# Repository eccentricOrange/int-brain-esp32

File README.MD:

# Integrated Brain ESP-IDF Component
This is the MCU firmware for a custom PCB designed to control, supply power to, and monitor a four-wheeled robot. It's built on a master-slave architecture, with an ESP32 as the slave and an SBC (such as an NVIDIA Jetson or Raspberry Pi) as the master.

Related projects:
-   [Integrated Brain PCB](https://github.com/eccentricOrange/int-brain)
-   [Integrated Brain Python Library](https://github.com/eccentricOrange/int-brain-sbc)

Note that this project has a lot of different registers, addresses, and buffers. These are referenced several times throughout the documentation, but in the interest of comprehensibility, they are all listed towards the end of the documentation only.

# Overall design
Let's get an overview of the different concepts and categories of stuff (such as functions) involved in this component.

## Direct and register-based tasks
In general, there are two types of functions in the component:

-   **Direct task**

    These functions are typical functions. You call them (and pass in arguments if relevant) and the function will try to do whatever you told it to. Exactly how it behaves is completely transparent in this scenario: for example, if you told motor 3 to move forward with a PWM of 127, that's exactly what the system will attempt to do, and nothing else.

-   **Register-based task**

    In the interest of having a flexible system that can establish duplex (two-way) communication with an SBC, there is an extensive system of registers and state variables. Many functions write to these, and many others read from them to decide what actions to perform. You (the programmer) doesn't have the luxury of specifying the 127 (PWM) or forward (direction) as literal values in this situation.

The Doxygen documentation for each function states its type, so you can easily tell which is which.

## Topics/themes

*   **PCA9635 PWM Demux**

    To overcome the low number of GPIOs in the ESP32, this project uses the PCA driver to give PWM signals to the motor drivers and their corresponding LEDs. There are methods around initializing the driver, setting it's mode, setting specific PWM values etc. These are all under `pca_driver.h`.

*   **Current sense**

    The motor drivers have a current sense output that can be read by the ESP32 (with the use of a shunt resistor). The current sense is read by the ADC and converted to a digital value. The initialization, calibration, and reading of the current sense are all under `current_sense.h`.

*   **Encoder**
    
    The motors have encoders that can be read by the ESP32 to provide their angular velocity. The initialization, reading, and resetting of the encoders are all under `encoder.h`.

*   **Control of the robot and that of the motors is separate**

    The PCA drivers file `pca_driver.h` is responsible for controlling the motors and LEDs, and tends to deal with the lower-level functions of one motor at a time. The `four-wheel-robot.h` file is responsible for controlling four motors at a time, and includes some functions to instead treat the system as a cohesive robot. Functions in `four-wheel-robot.h` use functions from `pca_driver.h` quite heavily.

*   **Structure**

    In general, "direct" functions are used to handle things like initialization and register-based functions are used to handle the actual tasks. Either these functions directly, or your custom functions, are expected to be registered as RTOS tasks using `xTaskCreate()` (built-in to FreeRTOS and ESP-IDF) since they will run perpetually.

# I2C Communication with the SBC
This is one of the relatively elaborate parts of the firmware, so it deserves some more attention. In general, the ESP32 acts as a slave to the SBC. The SBC can both issue commands to the ESP32, and request data such as sensor readings and motor status.

It is important you understand how this works, so we'll go over it in detail.

*   **The concept of a pseudo register**

    In the world of I2C-based devices, it is common for the slave to have a register. Each register then has a defined memory location (an address) and a clear purpose. For example, setting the value of the register at `0x00` sets the PCA driver mode, telling it what to do with further commands from the master.

    Since there is a wide variety of data we wish to transfer between the ESP32 and the SBC, this project adopts a similar system. Instead of dealing with actual memory addresses in the ESP32, we use a "pseudo register" system. To the SBC, this seems as though the ESP32 has registers like any ol' I2C device. However, in reality, it just places the byte that's supposed to the register address into a `switch() case` structure.

    Many other functions in the firmware behave in that way, so it's important to recognize what the term "register" refers to in this system. Unfortunately, devices like the PCA driver and the IMU do have true registers, so I'll provide a list of all pseudo later in this documentation.

    `int-brain-sbc-registers.h` gives the addresses of most of these pseudo registers that the SBC has to deal with. Additionally, addresses are split into sending and receiving addresses, to make it easier to determine what the I2C bus is doing at any given time.

*   **I2C buffers**

    Additionally, whenever the master (SBC) initiates a communication, it is expected that the first byte is the pseudo register address. The ESP32 will then read this byte and decide what to do based on it. While parsing, this byte is stored in `_sbc_i2c1_register`.

    Keeping in mind the interrupt-based nature of I2C communication in the ESP32 system \[[source](https://docs.espressif.com/projects/esp-idf/en/v5.3/esp32/api-reference/peripherals/i2c.html)\], two I2C buffers are defined in this system.

    *   One of them `_sbc_i2c1_receive_buffer` is the data (such as motor speeds) that should go from the SBC to the ESP32. When the ESP32 has finished reading the data, it is available in this buffer.
    *   The other `_sbc_i2c1_send_buffer` is the data (such as encoder positions) that should go from the ESP32 to the SBC. While parsing the pseudo register `_sbc_i2c1_register`, the ESP32 will fill this buffer with the relevant data, and the master can read it whenever it wants. Note that this is a FIFO buffer, so care should be taken that whatever data is written to it is read by the master (and not left to clog up the buffer).

# Motor command systems
Controlling a motor has two basic aspects: the direction and the speed, given as forward/backward/stop and a PWM value respectively.

Motor modes allow us to incorporate more functionality that can help in development of more safety features, make it easier to take emergency action, and issue the same speed to all motors at once.

These modes are controlled by a pseudo register, and pairs of bits define each mode.

## Safety modes
*   **Unsafe mode**

    The motor obeys your commands directly, without any modifications from the firmware. This is the default mode.

*   **Protect stall mode**
    
    A stall is defined either when the motor exceeds a certain current threshold or when the encoder position is not changing, given a PWM value. To protect the motor, it will be stopped if a stall is detected.

*   **Protect disconnect mode**
    
    If the motor is disconnected, the current sense will read zero, given a minimum PWM value. If this is detected, the motor will be stopped. Optionally, that specific motor's LED will blink to let you debug easily.

*   **Protect stall and disconnect mode**
        
    This is a combination of the two modes above. If either a stall or a disconnect is detected, the motor will be stopped.

## Speed modes
*   **Stop mode:** The motor will stop, regardless of the PWM value (PWM = 0).
*   **Max mode:** The motor will run at full speed, regardless of the PWM value (PWM = 255).
*   **Command speed mode:** The motor will run at the PWM value you specify for that particular motor.
*   **Speed register mode:** All motors will run at the same speed, given by the value in the speed register.

## Enable modes
This leverages the OUTPUT ENABLED pin of the PCA driver. If the driver is disabled, all PWM values will be 0, and all motors will stop.

This value for this mode may simply be enabled or disabled.

## Motor direction
The DRV8251A driver has the ability to actively brake the motor instead of letting it coast to a stop. This is done by setting the direction to brake. This gives us a total of four possible directions for each motor: idle, forward, backward, and brake.

## Motor command functions

| Function name | Speed control type | Direction control type | Safety mode | Speed mode | Enable mode |
| --- | --- | --- | --- | --- | --- |
| `set_motor_speeds()` | Array for individual speeds | [unused] | Not set-able | Not set-able | Not set-able |
| `set_common_motor_speed()` | Single speed for all motors | [unused] | Not set-able | Not set-able | Not set-able |
| `set_motor_directions()` | [unused] | Array for individual directions | Not set-able | Not set-able | Not set-able |
| `set_bot_direction()` | [unused] | Variable for unified robot direction | Not set-able | Not set-able | Not set-able |
| `set_motor_mode_register()` | [unused] | [unused] | Set-able by variable | Set-able by variable | Set-able by variable |
| `set_motor_safety_mode()` | [unused] | [unused] | Set-able by variable | [unused] | [unused] |
| `set_motor_speed_mode()` | [unused] | [unused] | [unused] | Set-able by variable | [unused] |
| `enable_motor_output()` | [unused] | [unused] | [unused] | [unused] | Forced to `ENABLED` |
| `disable_motor_output()` | [unused] | [unused] | [unused] | [unused] | Forced to `DISABLED` |

After calling any of these, you must also call `publish_motor_command()` to actually send the commands to the motors through the PCA driver.

# I2C Scheme

## Addresses

| Host | Slave | Address |
| --- | --- | --- |
| ESP32 | MPU9250 | 0x68 or 0x69 |
| ESP32 | PCA9635 | 0x40 |
| Raspberry Pi | ESP32 | 0x30 |

Note that in many of the registers below, the address is given as a range. In such cases, each address in range corresponds to a particular motor. This feature allows you to use a shorter I2C transmission if you do not want to address all motors at once.

## Raspberry Pi request from ESP32 (send) registers
*   `FIRST_SLAVE_REQUEST_ADDRESS = 0x00`
*   `LAST_SLAVE_REQUEST_ADDRESS = 0x9F`

| Description | "Register" | Data type | Length |
| --- | --- | --- | --- |
| Encoder positions | 0x10 | 4 bytes per motor (int) | 16 bytes |
| Encoder position per motor | 0x11 - 0x14 | 4 bytes (int) | 4 bytes |
| Motor speeds | 0x15 | 4 bytes per motor (int) | 16 bytes |
| Motor speed per motor | 0x16 - 0x19 | 4 bytes (int) | 4 bytes |
| Motor current | 0x20 | 4 bytes per motor (int) | 16 bytes |
| Motor current per motor | 0x21 - 0x24 | 4 bytes (int) | 16 bytes |
| Motor stall status | 0x30 | 1 byte total (bool) | 1 byte |
| Motor disconnect status | 0x31 | 1 byte total (bool) | 1 byte |
| IMU data (acceleration) | 0x40 | 4 bytes per axis (int) | 12 bytes |
| IMU data (gyroscope) | 0x41 | 4 bytes per axis (int) | 12 bytes |
| IMU data (magnetometer) | 0x42 | 4 bytes per axis (int) | 12 bytes |
| IMU data (quaternion) | 0x43 | 4 bytes per axis (int) | 16 bytes |
| Battery voltage | 0x50 | 4 bytes (int) | 4 bytes |

## Raspberry Pi command to ESP32 (receive) registers
*   `FIRST_SLAVE_COMMAND_ADDRESS = 0xA0`
*   `LAST_SLAVE_COMMAND_ADDRESS = 0xFF`

| Description | "Register" | Data type | Length |
| --- | --- | --- | --- |
| Motor operation mode | 0xA0 | 1 byte total (int) | 1 byte |
| Standard motor data | 0xA1 | 1 byte per motor + 1 byte (int + int) | 5 bytes |
| Standard motor data per motor | 0xA2 - 0xA5 | 2 bytes (int + int) | 2 bytes |
| Motor directions | 0xA6 | 1 byte total (int) | 1 byte |
| Motor direction per motor | 0xA7 - 0xAA | 1 byte (int) | 1 byte |
| Motor speeds | 0xAB | 1 byte per motor (int) | 4 bytes |
| Motor speed per motor | 0xAC - 0xAF | 1 byte (int) | 1 byte |
| Robot direction | 0xB0 | 1 byte total (int) | 1 byte |
| Common speed | 0xB1 | 2 bytes (int) | 2 bytes |

The "standard motor data" is simply means that the first byte specifies motor direction and next byte(s) specify the motor speed(s). This functionality is made available since it's common to send both these parameters together in practical robots.

## Bit breakdowns

### [0xB0] Robot direction
| Value | Description |
| --- | --- |
| 0 | Front |
| 1 | Back |
| 2 | Rotate clockwise |
| 3 | Rotate counterclockwise |
| 4 | Front left |
| 5 | Front right |
| 6 | Back left |
| 7 | Back right |

### [Common motor breakdown]
The motor stall status, disconnect status, and direction registers all obey this scheme. Two bits are used to specify the value for any one motor, so a single byte is sufficient for all four motors.

| Bit | Motor |
| --- | --- |
| 0, 1 | 0 |
| 2, 3 | 1 |
| 4, 5 | 2 |
| 6, 7 | 3 |

### [0x30] Motor stall status
| Value | Description |
| --- | --- |
| 00 | Not stalled |
| 01 | Stalled |
| 10 | [UNUSED] |
| 11 | [UNUSED] |

### [0x31] Motor disconnect status
| Value | Description |
| --- | --- |
| 00 | Connected |
| 01 | Disconnected |
| 10 | [UNUSED] |
| 11 | [UNUSED] |

### [0xA6] Motor directions
| Value | Description |
| --- | --- |
| 00 | Idle |
| 01 | Forward |
| 10 | Backward |
| 11 | Brake |

### [0xA0] Motor operation mode
This register does not follow the common motor breakdown scheme. Instead, each pair of bits controls a different aspect of the motor operation mode. The modes set here apply to all motors.

#### Bits 1, 0: Safety
| Value | Description |
| --- | --- |
| 00 | Unsafe |
| 01 | Protect stall |
| 10 | Protect disconnect |
| 11 | Protect stall and disconnect |

#### Bits 3, 2: Speed
| Value | Description |
| --- | --- |
| 00 | 0 (stop) |
| 01 | 255 (max) |
| 10 | command speed |
| 11 | speed register (0xB1) |

#### Bit 5, 4: Enable
| Value | Description |
| --- | --- |
| 00 | Disable |
| 01 | Enable |
| 10 | [UNUSED] |
| 11 | [UNUSED] |

#### Bits 6 - 7: Unused

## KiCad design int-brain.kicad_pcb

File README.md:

# Integrated Brain
The Integrated Brain is a custom PCB designed to control, supply power to, and monitor a four-wheeled robot. It's built on a master-slave architecture, with an ESP32 as the slave and an SBC (such as an NVIDIA Jetson or Raspberry Pi) as the master.

## Features
| Feature | Description | Specification |
| --- | --- | --- |
| ESP32 Microcontroller | Header for external ESP32 | **ESP32-WROOM-32** 38-pin dev board |
| Motor Drivers | Built on to the PCB | 4x **DRV8251A**. While the 8251A can provide up to **4.1 A**, the PCB design is compatible with other DRV series drivers too. |
| Motor Indicator LEDs | Built on to the PCB | 4x, user-controllable through the PWM demux. |
| Motor Encoder | Support for external quadrature encoders | Connect through JST-4 connectors, directly to ESP32 GPIO. |
| Motor Current Sense | Built on to the PCB | Using the 8251A's feature, connected to the ESP32 ADCs. Additional support for shunt resistor and current-sense amplifier in case of different motor driver IC. |
| IMU | Headers for external IMU | **MPU9250** connected over I2C0 to the ESP32 |
| Internal power supply | Built on to the PCB | **5V (5A)** (TPS5450 buck) and **3.3V** (AMS1117) power supplies for the ESP32 and other peripherals. |
| SBC Power supply | Built on to the PCB | **5V (5A)** (TPS5450 buck) power supply for the SBC., via USB-A. |
| PWM Demux | Built on to the PCB | **PCA9635** connected over I2C0 to the ESP32. Spare PWM channels are *not* exposed. |

## Overall system architecture

The ESP32 microcontroller handles the interaction between all the different peripherals, along with low-level control loops and signal processing. Telemetry and IMU data is fed directly to this ESP32.

Motors are driven using full H-bridge drivers, with built-in braking and current-sense capabilities. These motor drivers are controlled through a PWM demux, owing to the requirement for a large number of PWM pins.

Signals on-board are handled over I2C0, where the ESP32 acts as the master. It is configured as a slave on the I2C1 bus, which is used to communicate with an SBC. I2C0, I2C1, as well as an additional UART port are all exposed with JST connectors.

## Responsibilities of the ESP32 microcontroller
*   Receive commands from the SBC over I2C1
*   Control the motor drivers and the motor indicator LEDs, using the PCA9635 PWM mux over I2C0
*   Read the motor encoders and the motor current sense
*   Read the IMU data, over I2C0
*   Read the battery voltage (using a voltage divider)
*   Run the internal PID loop for motor control (RPM using encoder data)
*   Handle motor protection in case of stall (detected by encoder data) or disconnect (detected by current sense)
*   Filter IMU data
*   Send data to the SBC over I2C1 when requested

## Motor driver design
The system is designed to use the Texas Instruments DRV8251A motor driver, which is capable of driving up to 4.1 A.

Provided that DRV8251A (or any other DRV82\*\*A) drivers are used, we can leverage both the current-sense and current-limiting capabilities of the chip. Since the driver handles current attenuation, we may use a low-power high-resistance shunt resistor to generate a voltage drop. Additionally, using this as a voltage divider, we may supply a current limit; beyond this limit, the driver will automatically throttle voltage.

However, if an alternate motor driver is used (such as DRV8251), the system is designed to support a high-power low-resistance shunt resistor and a current-sense amplifier. The current-limiting feature of the driver will not be used in this case.

The equations to calculate these resistances were derived from the DRV8251A data sheet, and are provided in the schematics.

## Power supply design

The system is designed to take either 12 V or 24 V DC power. This can be given by either a DC barrel jack or an XT60 connector, designed with the intention of using a LiPo battery. This power must go through two diodes (hooked up in parallel) before being used for any purpose.

Conversion to 5 V and 3.3 V is handled on-board. The buck converter responsible for supplying power to the SBC is isolated from the rest of the system for increased stability.

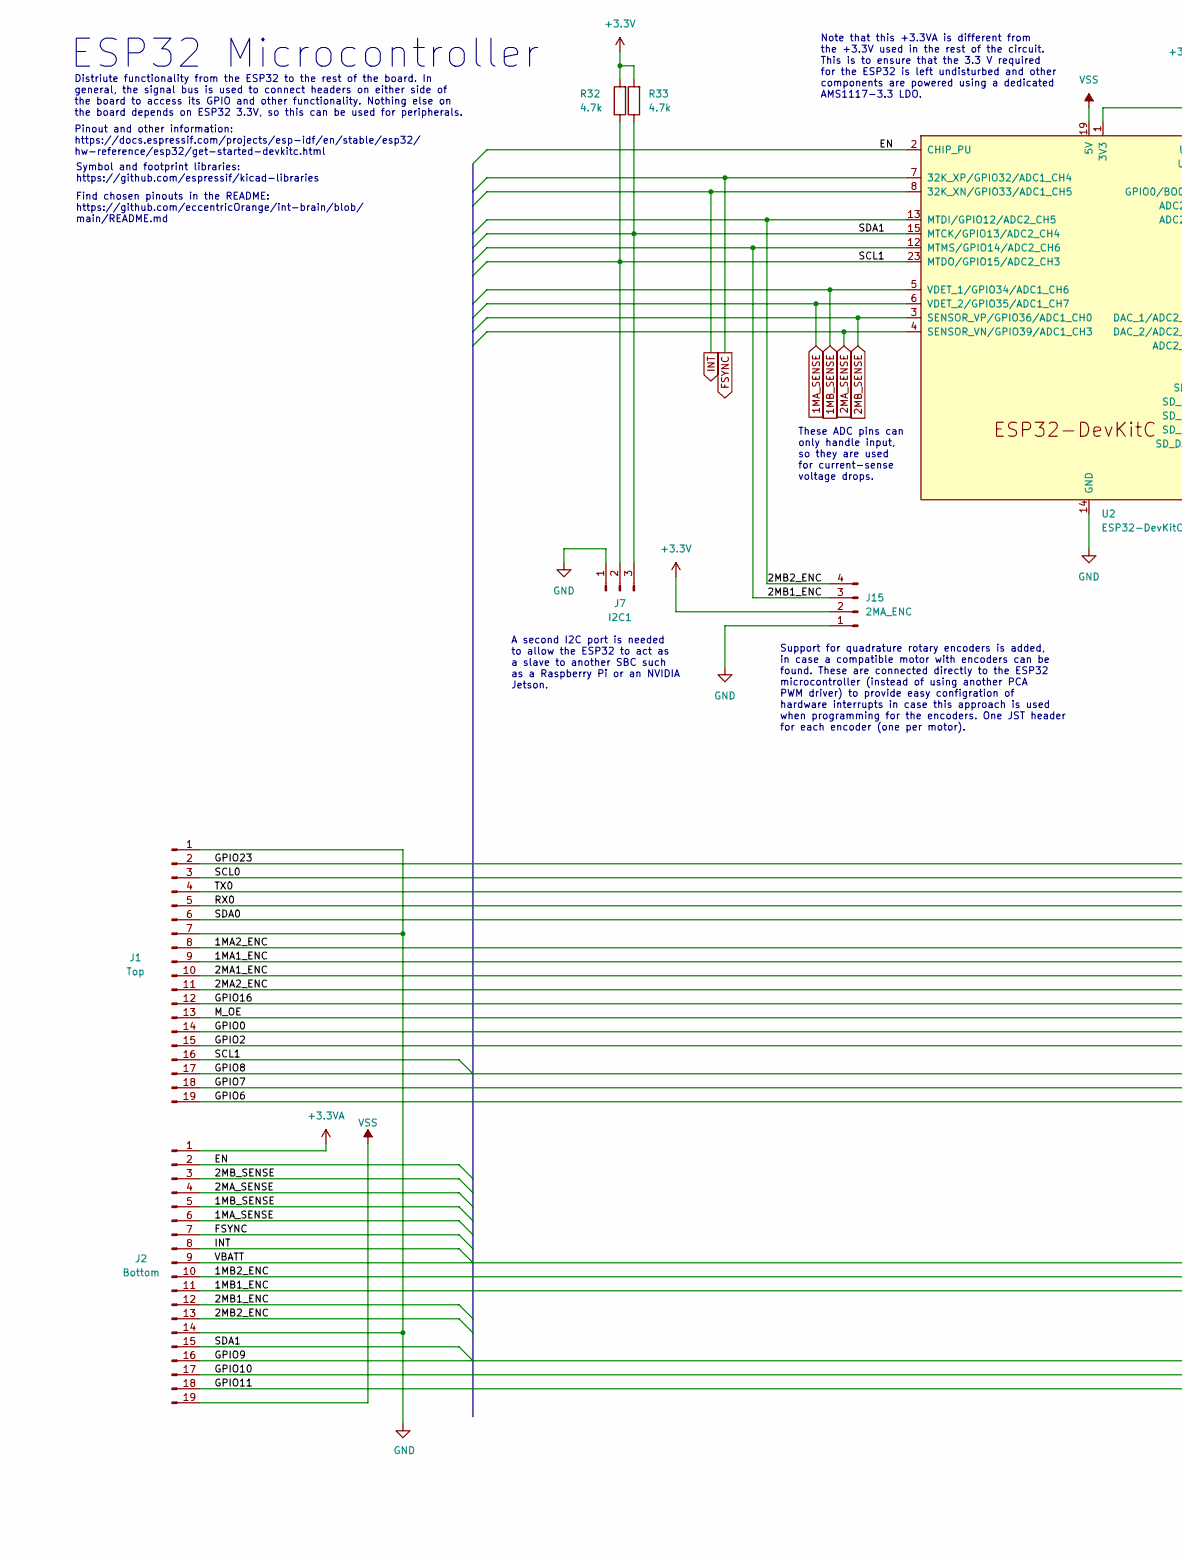
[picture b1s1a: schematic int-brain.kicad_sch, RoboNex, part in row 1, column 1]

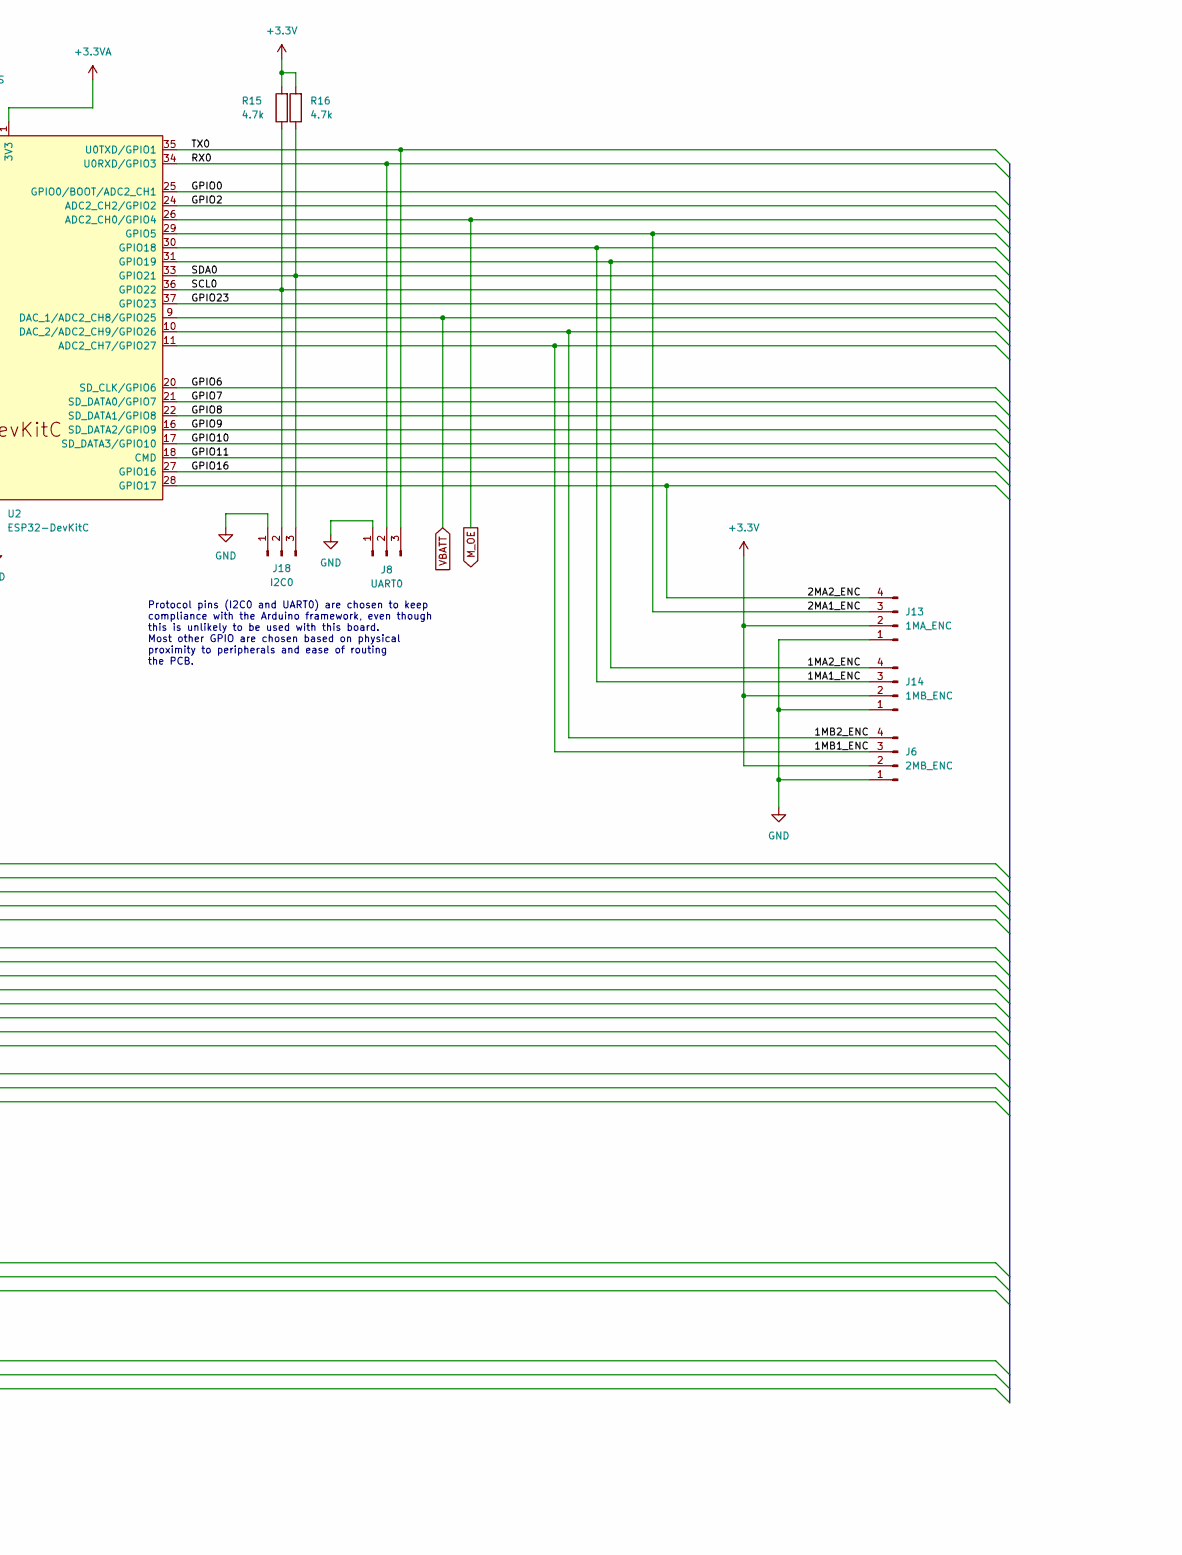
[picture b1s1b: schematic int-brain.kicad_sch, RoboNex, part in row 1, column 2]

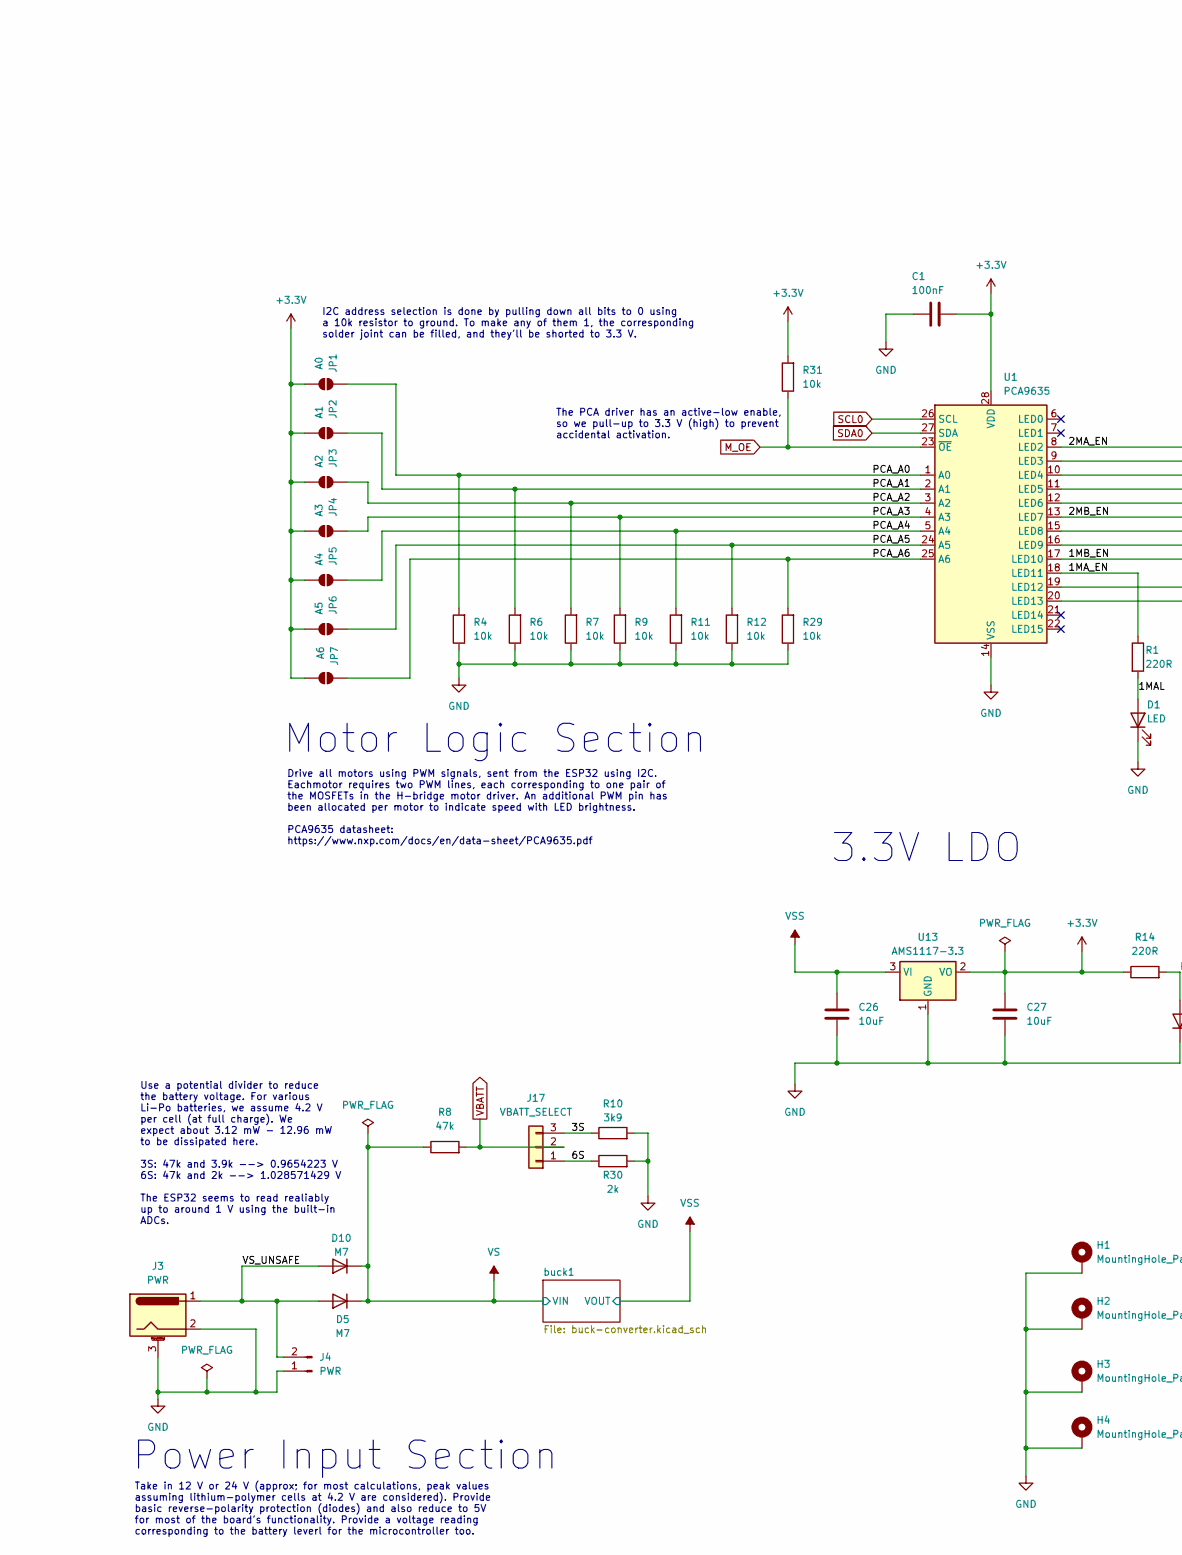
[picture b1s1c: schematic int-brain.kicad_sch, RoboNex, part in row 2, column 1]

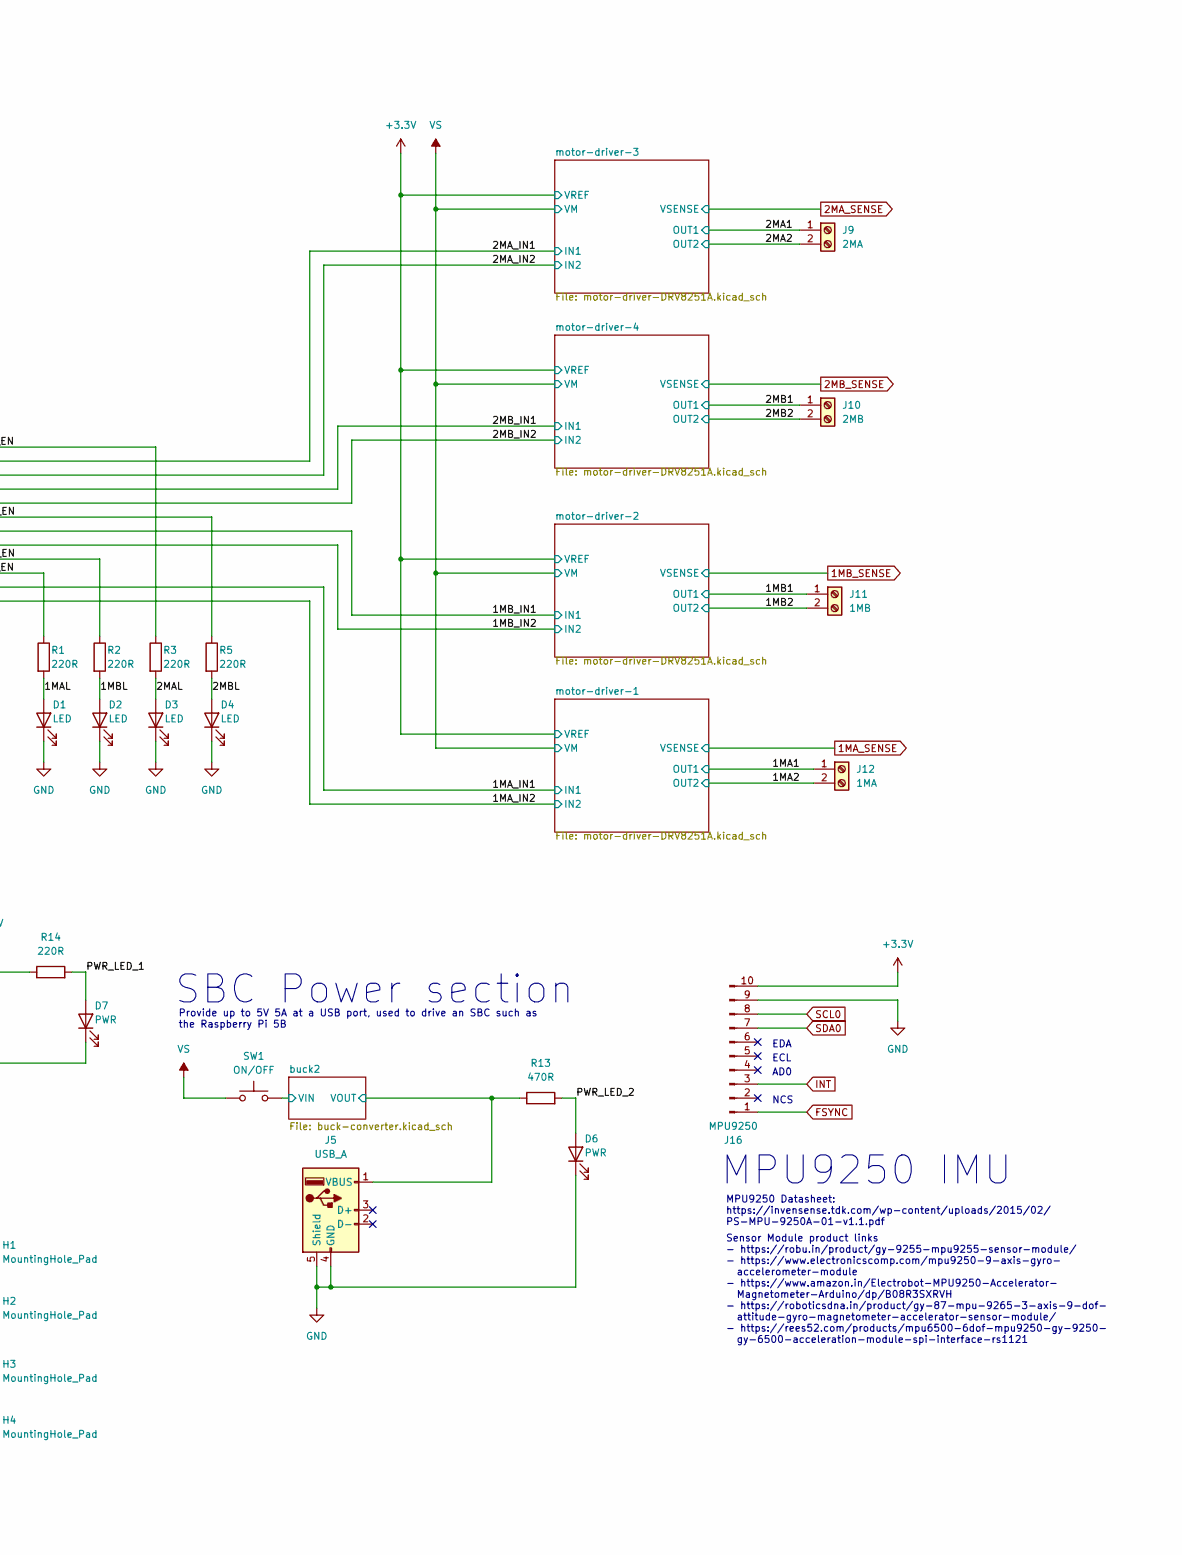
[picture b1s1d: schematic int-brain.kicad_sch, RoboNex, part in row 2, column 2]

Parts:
C1: 100nF; C_0805_2012Metric_Pad1.18x1.45mm_HandSolder
C26, C27: 10uF; C_1206_3216Metric_Pad1.33x1.80mm_HandSolder
D1, D2, D3, D4: LED; LED_1206_3216Metric_Pad1.42x1.75mm_HandSolder
D5, D10: M7; D_SMA_Handsoldering
D6, D7: PWR; LED_1206_3216Metric_Pad1.42x1.75mm_HandSolder
H1, H2, H3, H4: MountingHole_Pad; MountingHole_3.2mm_M3_Pad_Via
J1: Top; PinHeader_1x19_P2.54mm_Vertical
J2: Bottom; PinHeader_1x19_P2.54mm_Vertical
J3: PWR; BarrelJack_Horizontal
J4: PWR; AMASS_XT60IPW-M_1x03_P7.20mm_Horizontal
J5: USB_A; USB_A_Molex_67643_Horizontal
J6: 2MB_ENC; JST_EH_B4B-EH-A_1x04_P2.50mm_Vertical
J7: I2C1; JST_EH_B3B-EH-A_1x03_P2.50mm_Vertical
J8: UART0; JST_EH_B3B-EH-A_1x03_P2.50mm_Vertical
J9: 2MA; TerminalBlock_Philmore_TB132_1x02_P5.00mm_Horizontal
J10: 2MB; TerminalBlock_Philmore_TB132_1x02_P5.00mm_Horizontal
J11: 1MB; TerminalBlock_Philmore_TB132_1x02_P5.00mm_Horizontal
J12: 1MA; TerminalBlock_Philmore_TB132_1x02_P5.00mm_Horizontal
J13: 1MA_ENC; JST_EH_B4B-EH-A_1x04_P2.50mm_Vertical
J14: 1MB_ENC; JST_EH_B4B-EH-A_1x04_P2.50mm_Vertical
J15: 2MA_ENC; JST_EH_B4B-EH-A_1x04_P2.50mm_Vertical
J16: MPU9250; PinHeader_1x10_P2.54mm_Vertical
J17: VBATT_SELECT; PinHeader_1x03_P2.54mm_Vertical
J18: I2C0; JST_EH_B3B-EH-A_1x03_P2.50mm_Vertical
JP1: A0; SolderJumper-2_P1.3mm_Open_Pad1.0x1.5mm
JP2: A1; SolderJumper-2_P1.3mm_Open_Pad1.0x1.5mm
JP3: A2; SolderJumper-2_P1.3mm_Open_Pad1.0x1.5mm
JP4: A3; SolderJumper-2_P1.3mm_Open_Pad1.0x1.5mm
JP5: A4; SolderJumper-2_P1.3mm_Open_Pad1.0x1.5mm
JP6: A5; SolderJumper-2_P1.3mm_Open_Pad1.0x1.5mm
JP7: A6; SolderJumper-2_P1.3mm_Open_Pad1.0x1.5mm
R1, R2, R3, R5, R14: 220R; R_1206_3216Metric_Pad1.30x1.75mm_HandSolder
R4, R6, R7, R9, R11, R12, R29, R31: 10k; R_1206_3216Metric_Pad1.30x1.75mm_HandSolder
R8: 47k; R_1206_3216Metric_Pad1.30x1.75mm_HandSolder
R10: 3k9; R_1206_3216Metric_Pad1.30x1.75mm_HandSolder
R13: 470R; R_1206_3216Metric_Pad1.30x1.75mm_HandSolder
R15, R16, R32, R33: 4.7k; R_1206_3216Metric_Pad1.30x1.75mm_HandSolder
R30: 2k; R_1206_3216Metric_Pad1.30x1.75mm_HandSolder
SW1: ON/OFF; SW_PUSH_6mm_H5mm
U1: PCA9635; TSSOP-28_4.4x9.7mm_P0.65mm
U2: ESP32-DevKitC; ESP32-DevKitC-slim
U13: AMS1117-3.3; SOT-223-3_TabPin2

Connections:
1MB_SENSE: J2.5, U2.5 (VDET_1/GPIO34/ADC1_CH6); also elsewhere on the board
2MA_SENSE: J2.4, U2.4 (SENSOR_VN/GPIO39/ADC1_CH3); also elsewhere on the board
2MB_SENSE: J2.3, U2.3 (SENSOR_VP/GPIO36/ADC1_CH0); also elsewhere on the board
+3.3V: C1.1, C27.1, J6.2, J13.2, J14.2, J15.2, J16.10, JP1.1 (A), JP2.1 (A), JP3.1 (A), JP4.1 (A), JP5.1 (A), JP6.1 (A), JP7.1 (A), R14.1, R15.2, R16.2, R31.2, R32.2, R33.2, U1.28 (VDD), U13.2 (VO); also elsewhere on the board
+3.3VA: J2.1, U2.1 (3V3)
/1MA1: J12.1; also elsewhere on the board
/1MA1_ENC: J1.9, J14.3, U2.30 (GPIO18)
/1MA2: J12.2; also elsewhere on the board
/1MA2_ENC: J1.8, J14.4, U2.31 (GPIO19)
/1MAL: D1.2 (A), R1.2
/1MA_EN: R1.1, U1.18 (LED11)
/1MA_IN1: U1.19 (LED12); also elsewhere on the board
/1MA_IN2: U1.20 (LED13); also elsewhere on the board
/1MB1: J11.1; also elsewhere on the board
/1MB1_ENC: J2.11, J6.3, U2.11 (ADC2_CH7/GPIO27)
/1MB2: J11.2; also elsewhere on the board
/1MB2_ENC: J2.10, J6.4, U2.10 (DAC_2/ADC2_CH9/GPIO26)
/1MBL: D2.2 (A), R2.2
/1MB_EN: R2.1, U1.17 (LED10)
/1MB_IN1: U1.15 (LED8); also elsewhere on the board
/1MB_IN2: U1.16 (LED9); also elsewhere on the board
/2MA1: J9.1; also elsewhere on the board
/2MA1_ENC: J1.10, J13.3, U2.29 (GPIO5)
/2MA2: J9.2; also elsewhere on the board
/2MA2_ENC: J1.11, J13.4, U2.28 (GPIO17)
/2MAL: D3.2 (A), R3.2
/2MA_EN: R3.1, U1.8 (LED2)
/2MA_IN1: U1.9 (LED3); also elsewhere on the board
/2MA_IN2: U1.10 (LED4); also elsewhere on the board
/2MB1: J10.1; also elsewhere on the board
/2MB1_ENC: J2.12, J15.3, U2.12 (MTMS/GPIO14/ADC2_CH6)
/2MB2: J10.2; also elsewhere on the board
/2MB2_ENC: J2.13, J15.4, U2.13 (MTDI/GPIO12/ADC2_CH5)
/2MBL: D4.2 (A), R5.2
/2MB_EN: R5.1, U1.13 (LED7)
/2MB_IN1: U1.11 (LED5); also elsewhere on the board
/2MB_IN2: U1.12 (LED6); also elsewhere on the board
/3S: J17.3, R10.1
/6S: J17.1, R30.1
/EN: J2.2, U2.2 (CHIP_PU)
/GPIO0: J1.14, U2.25 (GPIO0/BOOT/ADC2_CH1)
/GPIO2: J1.15, U2.24 (ADC2_CH2/GPIO2)
/GPIO6: J1.19, U2.20 (SD_CLK/GPIO6)
/GPIO7: J1.18, U2.21 (SD_DATA0/GPIO7)
/GPIO8: J1.17, U2.22 (SD_DATA1/GPIO8)
/GPIO9: J2.16, U2.16 (SD_DATA2/GPIO9)
/GPIO10: J2.17, U2.17 (SD_DATA3/GPIO10)
/GPIO11: J2.18, U2.18 (CMD)
/GPIO16: J1.12, U2.27 (GPIO16)
/GPIO23: J1.2, U2.37 (GPIO23)
/PCA_A0: JP1.2 (B), R4.2, U1.1 (A0)
/PCA_A1: JP2.2 (B), R6.2, U1.2 (A1)
/PCA_A2: JP3.2 (B), R7.2, U1.3 (A2)
/PCA_A3: JP4.2 (B), R9.2, U1.4 (A3)
/PCA_A4: JP5.2 (B), R11.2, U1.5 (A4)
/PCA_A5: JP6.2 (B), R12.2, U1.24 (A5)
/PCA_A6: JP7.2 (B), R29.2, U1.25 (A6)
/PWR_LED_1: D7.2 (A), R14.2
/PWR_LED_2: D6.2 (A), R13.2
/RX0: J1.5, J8.2, U2.34 (U0RXD/GPIO3)
/SCL1: J1.16, J7.2, R32.1, U2.23 (MTDO/GPIO15/ADC2_CH3)
/SDA1: J2.15, J7.3, R33.1, U2.15 (MTCK/GPIO13/ADC2_CH4)
/TX0: J1.4, J8.3, U2.35 (U0TXD/GPIO1)
/VS_UNSAFE: D5.2 (A), D10.2 (A), J3.1, J4.2
/buck2/BUCK_VIN: SW1.2; also elsewhere on the board
/buck2/VOUT: J5.1 (VBUS), R13.1; also elsewhere on the board
FSYNC: J2.7, J16.1, U2.7 (32K_XP/GPIO32/ADC1_CH4)
GND: C1.2, C26.2, C27.2, D1.1 (K), D2.1 (K), D3.1 (K), D4.1 (K), D6.1 (K), D7.1 (K), H1.1, H2.1, H3.1, H4.1, J1.1, J1.7, J2.14, J3.2, J3.3 (MountPin), J4.1, J5.4 (GND), J5.5 (Shield), J6.1, J7.1, J8.1, J13.1, J14.1, J15.1, J16.9, J18.1, R4.1, R6.1, R7.1, R9.1, R10.2, R11.1, R12.1, R29.1, R30.2, U1.14 (VSS), U2.14 (GND), U2.32 (GND), U2.38 (GND), U13.1 (GND); also elsewhere on the board
INT: J2.8, J16.3, U2.8 (32K_XN/GPIO33/ADC1_CH5)
M_OE: J1.13, R31.1, U1.23 (~OE), U2.26 (ADC2_CH0/GPIO4)
SCL0: J1.3, J16.8, J18.2, R15.1, U1.26 (SCL), U2.36 (GPIO22)
SDA0: J1.6, J16.7, J18.3, R16.1, U1.27 (SDA), U2.33 (GPIO21)
VBATT: J2.9, J17.2, R8.2, U2.9 (DAC_1/ADC2_CH8/GPIO25)
VS: D5.1 (K), D10.1 (K), R8.1, SW1.1; also elsewhere on the board
VSS: C26.1, J2.19, U2.19 (5V), U13.3 (VI); also elsewhere on the board

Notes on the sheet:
The PCA driver has an active-low enable, so we pull-up to 3.3 V (high) to prevent accidental activation.
PCA9635 datasheet: https://www.nxp.com/docs/en/data-sheet/PCA9635.pdf
Find chosen pinouts in the README: https://github.com/eccentricOrange/int-brain/blob/ main/README.md
NCS
Motor Logic Section
AD0
SBC Power section
Note that this +3.3VA is different from the +3.3V used in the rest of the circuit. This is to ensure that the 3.3 V required for the ESP32 is left undisturbed and other components are powered using a dedicated AMS1117-3.3 LDO.
Sensor Module product links - https://robu.in/product/gy-9255-mpu9255-sensor-module/ - https://www.electronicscomp.com/mpu9250-9-axis-gyro- accelerometer-module - https://www.amazon.in/Electrobot-MPU9250-Accelerator- Magnetometer-Arduino/dp/B08R3SXRVH - https://roboticsdna.in/product/gy-87-mpu-9265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
Support for quadrature rotary encoders is added, in case a compatible motor with encoders can be found. These are connected directly to the ESP32 microcontroller (instead of using another PCA PWM driver) to provide easy configration of hardware interrupts in case this approach is used when programm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
Drive all motors using PWM signals, sent from the ESP32 using I2C. Eachmotor requires two PWM lines, each corresponding to one pair of the MOSFETs in the H-bridge motor driver. An additional PWM pin has been allocated per motor to indicate speed with LED brightness.
MPU9250 Datasheet: https://invensense.tdk.com/wp-content/uploads/2015/02/ PS-MPU-9250A-01-v1.1.pdf
Take in 12 V or 24 V (approx; for most calculations, peak values assuming lithium-polymer cells at 4.2 V are considered). Provide basic reverse-polarity protection (diodes) and also reduce to 5V for most of the board's functionality. Provide a voltage reading corresponding to the battery leverl for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
EDA
Symbol and footprint libraries: https://github.com/espressif/kicad-libraries
Use a potential divider to reduce the battery voltage. For various Li-Po batteries, we assume 4.2 V per cell (at full charge). We expect about 3.12 mW - 12.96 mW to be dissipated here. 3S: 47k and 3.9k --> 0.9654223 V 6S: 47k and 2k --> 1.028571429 V The ESP32 seems to read realiably up to around 1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
ECL
Protocol pins (I2C0 and UART0) are chosen to keep compliance with the Arduino framework, even though this is unlikely to be used with this board. Most other GPIO are chosen based on physical proximity to peripherals and ease of routing the PCB.
ESP32 Microcontroller
Provide up to 5V 5A at a USB port, used to drive an SBC such as the Raspberry Pi 5B
Pinout and other information: https://docs.espressif.com/projects/esp-idf/en/stable/esp32/ hw-reference/esp32/get-started-devkitc.html
Distriute functionality from the ESP32 to the rest of the board. In general, the signal bus is used to connect headers on either side of the board to access its GPIO and other functionality. Nothing else on the board depends on ESP32 3.3V, so this can be used for peripherals.
These ADC pins can only handle input, so they are used for current-sense voltage drops.
3.3V LDO
I2C address selection is done by pulling down all bits to 0 using a 10k resistor to ground. To make any of them 1, the corresponding solder joint can be filled, and they'll be shorted to 3.3 V.
A second I2C port is needed to allow the ESP32 to act as a slave to another SBC such as a Raspberry Pi or an NVIDIA Jetson.
Power Input Section
MPU9250 IMU

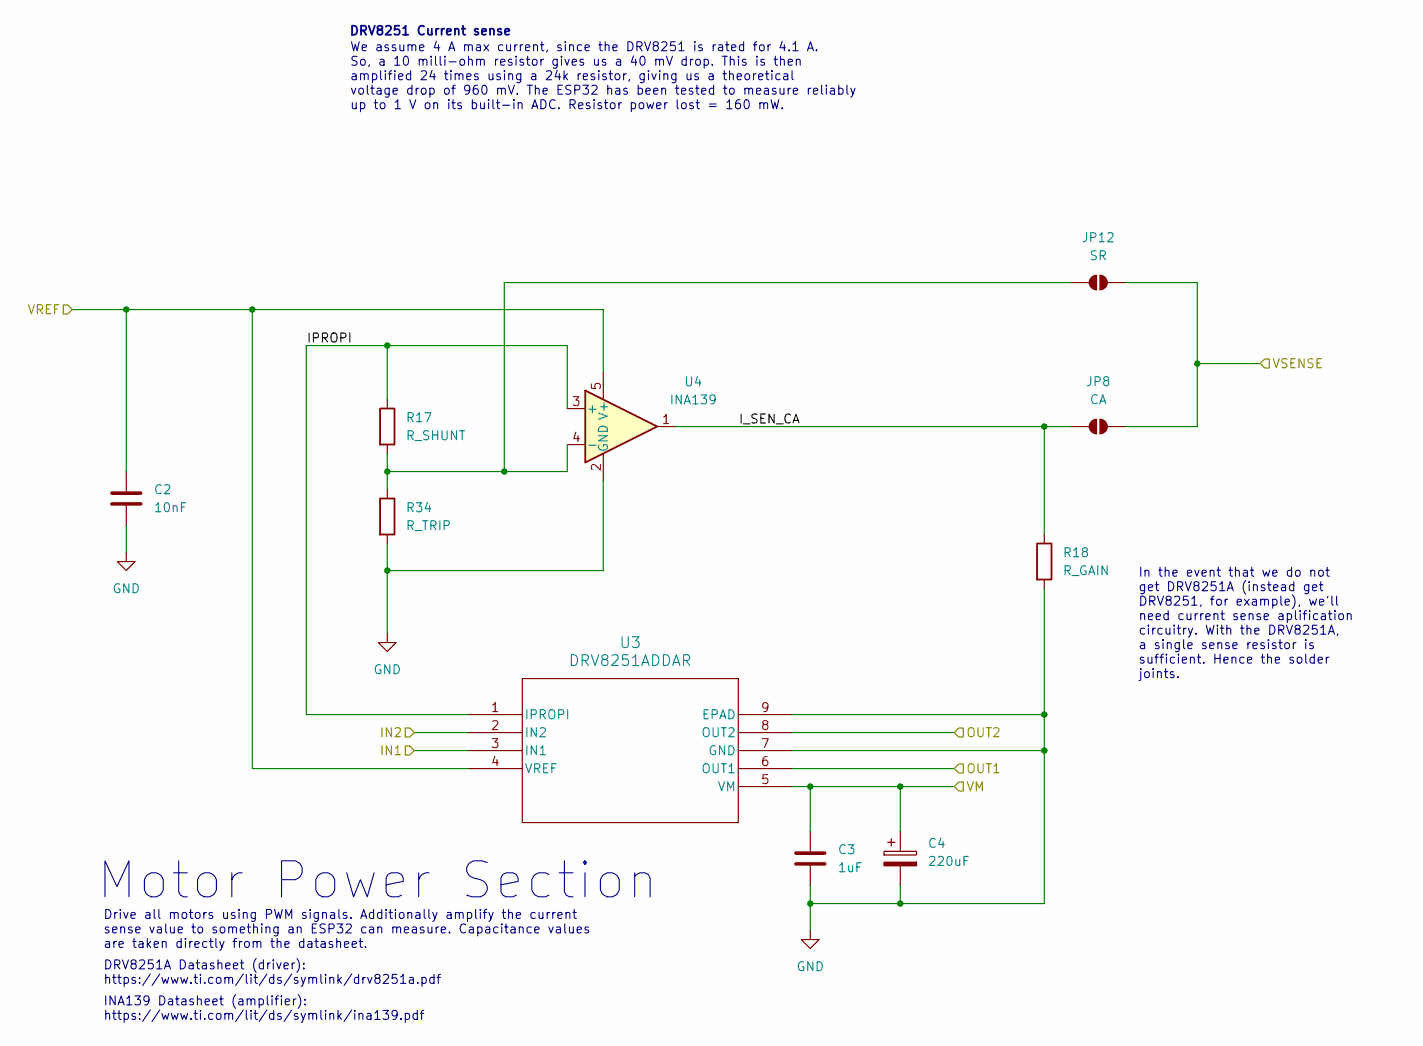
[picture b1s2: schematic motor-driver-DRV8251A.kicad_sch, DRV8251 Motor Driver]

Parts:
C2: 10nF; C_0805_2012Metric_Pad1.18x1.45mm_HandSolder
C3: 1uF; C_0805_2012Metric_Pad1.18x1.45mm_HandSolder
C4: 220uF; CP_Elec_8x10.5
JP8: CA; SolderJumper-2_P1.3mm_Open_Pad1.0x1.5mm
JP12: SR; SolderJumper-2_P1.3mm_Open_Pad1.0x1.5mm
R17: R_SHUNT; R_2512_6332Metric_Pad1.40x3.35mm_HandSolder
R18: R_GAIN; R_1206_3216Metric_Pad1.30x1.75mm_HandSolder
R34: R_TRIP; R_1206_3216Metric_Pad1.30x1.75mm_HandSolder
U3: DRV8251ADDAR; SOIC-8-1EP_3.9x4.9mm_P1.27mm_EP2.29x3mm_ThermalVias
U4: INA139; SOT-23-5_HandSoldering

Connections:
+3.3V: C2.1, U3.4 (VREF), U4.5 (V+); also elsewhere on the board
/1MB1: U3.6 (OUT1); also elsewhere on the board
/1MB2: U3.8 (OUT2); also elsewhere on the board
/1MB_IN1: U3.3 (IN1); also elsewhere on the board
/1MB_IN2: U3.2 (IN2); also elsewhere on the board
/motor-driver-2/IPROPI: R17.1, U3.1 (IPROPI), U4.3 (+)
GND: C2.2, C3.2, C4.2, R18.2, R34.2, U3.7 (GND), U3.9 (EPAD), U4.2 (GND); also elsewhere on the board
VS: C3.1, C4.1, U3.5 (VM); also elsewhere on the board

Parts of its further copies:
C5, C12, C19: 10nF; C_0805_2012Metric_Pad1.18x1.45mm_HandSolder
C6, C13, C20: 1uF; C_0805_2012Metric_Pad1.18x1.45mm_HandSolder
C7, C14, C21: 220uF; CP_Elec_8x10.5
JP9, JP10, JP11: CA; SolderJumper-2_P1.3mm_Open_Pad1.0x1.5mm
JP13, JP14, JP15: SR; SolderJumper-2_P1.3mm_Open_Pad1.0x1.5mm
R19, R23, R27: R_SHUNT; R_2512_6332Metric_Pad1.40x3.35mm_HandSolder
R20, R24, R28: R_GAIN; R_1206_3216Metric_Pad1.30x1.75mm_HandSolder
R35, R36, R37: R_TRIP; R_1206_3216Metric_Pad1.30x1.75mm_HandSolder
U5, U8, U11: DRV8251ADDAR; SOIC-8-1EP_3.9x4.9mm_P1.27mm_EP2.29x3mm_ThermalVias
U6, U9, U12: INA139; SOT-23-5_HandSoldering

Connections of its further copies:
1MB_SENSE: JP9.1 (A), JP13.2 (B); also elsewhere on the board
2MA_SENSE: JP10.1 (A), JP14.2 (B); also elsewhere on the board
2MB_SENSE: JP11.1 (A), JP15.2 (B); also elsewhere on the board
+3.3V: C5.1, C12.1, C19.1, U5.4 (VREF), U6.5 (V+), U8.4 (VREF), U9.5 (V+), U11.4 (VREF), U12.5 (V+); also elsewhere on the board
/1MA1: U8.6 (OUT1); also elsewhere on the board
/1MA2: U8.8 (OUT2); also elsewhere on the board
/1MA_IN1: U8.3 (IN1); also elsewhere on the board
/1MA_IN2: U8.2 (IN2); also elsewhere on the board
/2MA1: U5.6 (OUT1); also elsewhere on the board
/2MA2: U5.8 (OUT2); also elsewhere on the board
/2MA_IN1: U5.3 (IN1); also elsewhere on the board
/2MA_IN2: U5.2 (IN2); also elsewhere on the board
/2MB1: U11.6 (OUT1); also elsewhere on the board
/2MB2: U11.8 (OUT2); also elsewhere on the board
/2MB_IN1: U11.3 (IN1); also elsewhere on the board
/2MB_IN2: U11.2 (IN2); also elsewhere on the board
/motor-driver-1/IPROPI: R23.1, U8.1 (IPROPI), U9.3 (+)
/motor-driver-3/IPROPI: R19.1, U5.1 (IPROPI), U6.3 (+)
/motor-driver-3/I_SEN_CA: JP10.2 (B), R20.1, U6.1
/motor-driver-3/I_SEN_SR: JP14.1 (A), R19.2, R36.1, U6.4 (-)
/motor-driver-4/IPROPI: R27.1, U11.1 (IPROPI), U12.3 (+)
/motor-driver-4/I_SEN_CA: JP11.2 (B), R28.1, U12.1
/motor-driver-4/I_SEN_SR: JP15.1 (A), R27.2, R37.1, U12.4 (-)
GND: C5.2, C6.2, C7.2, C12.2, C13.2, C14.2, C19.2, C20.2, C21.2, R20.2, R24.2, R28.2, R35.2, R36.2, R37.2, U5.7 (GND), U5.9 (EPAD), U6.2 (GND), U8.7 (GND), U8.9 (EPAD), U9.2 (GND), U11.7 (GND), U11.9 (EPAD), U12.2 (GND); also elsewhere on the board
VS: C6.1, C7.1, C13.1, C14.1, C20.1, C21.1, U5.5 (VM), U8.5 (VM), U11.5 (VM); also elsewhere on the board

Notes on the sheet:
DRV8251 Current sense
In the event that we do not get DRV8251A (instead get DRV8251, for example), we'll need current sense aplification circuitry. With the DRV8251A, a single sense resistor is sufficient. Hence the solder joints.
Motor Power Section
We assume 4 A max current, since the DRV8251 is rated for 4.1 A. So, a 10 milli-ohm resistor gives us a 40 mV drop. This is then amplified 24 times using a 24k resistor, giving us a theoretical voltage drop of 960 mV. The ESP32 has been tested to measure reliably up to 1 V on its built-in ADC. Resi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
DRV8251A Datasheet (driver): https://www.ti.com/lit/ds/symlink/drv8251a.pdf
INA139 Datasheet (amplifier): https://www.ti.com/lit/ds/symlink/ina139.pdf
Drive all motors using PWM signals. Additionally amplify the current sense value to something an ESP32 can measure. Capacitance values are taken directly from the datasheet.
